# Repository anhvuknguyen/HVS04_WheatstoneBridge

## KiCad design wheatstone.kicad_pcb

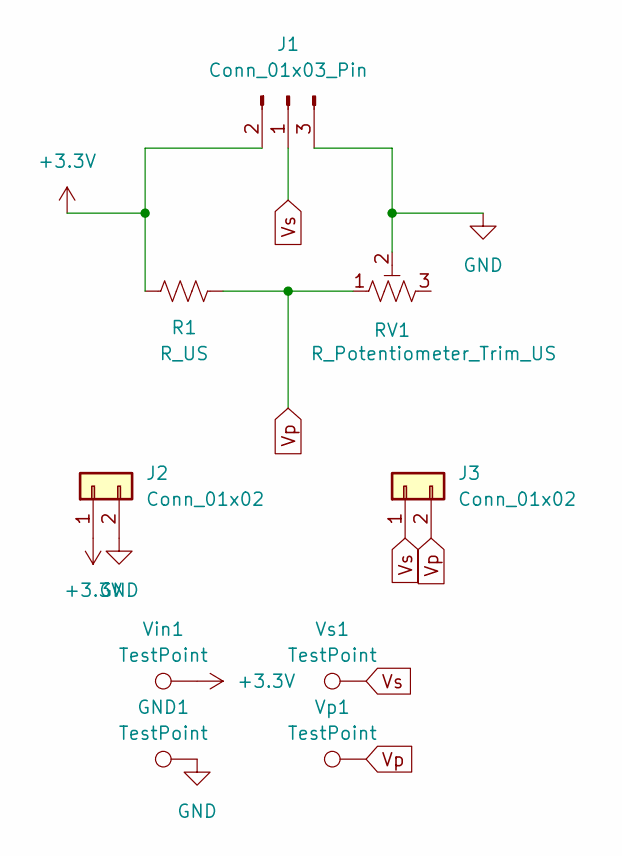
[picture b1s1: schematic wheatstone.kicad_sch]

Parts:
GND1: TestPoint; TestPoint_THTPad_D2.5mm_Drill1.2mm
J1: Conn_01x03_Pin; HVS_04
J2, J3: Conn_01x02; 46622-02YY
R1: R_US; R_Axial_DIN0207_L6.3mm_D2.5mm_P10.16mm_Horizontal
RV1: R_Potentiometer_Trim_US; PV36X101C01B00
Vin1: TestPoint; TestPoint_THTPad_D2.5mm_Drill1.2mm
Vp1: TestPoint; TestPoint_THTPad_D2.5mm_Drill1.2mm
Vs1: TestPoint; TestPoint_THTPad_D2.5mm_Drill1.2mm

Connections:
+3.3V: J1.2, J2.1, R1.2, Vin1.1 (1_1)
GND: GND1.1 (1_1), J1.3, J2.2, RV1.2
Vp: J3.2, R1.1, RV1.1, Vp1.1 (1_1)
Vs: J1.1, J3.1, Vs1.1 (1_1)

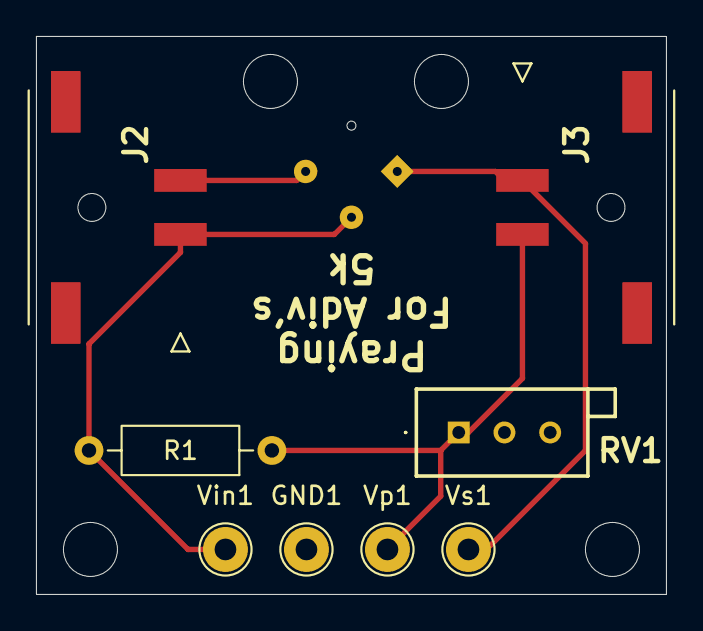
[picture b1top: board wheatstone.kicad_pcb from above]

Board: 2 copper layers, 35.0 x 31.0 mm, 9 parts (1 on the bottom side), 4 nets.

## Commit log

2026-04-11 implemented PCB
2026-04-14 final touches
